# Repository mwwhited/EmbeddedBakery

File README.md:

# Embedded Bakery

## Summary

This is a collection of various electronics and microprocessor projects including PAL, FPGA, CPLD, and microcontroller experiments.

## Repository Structure

```
src/
├── arduino/          # Arduino sketches and libraries
├── AVR/              # AVR microcontroller projects (ATmega, ATtiny)
├── ESP8266/          # ESP8266 WiFi module projects
├── STM32/            # STM32 ARM microcontroller projects
├── PIC/              # Microchip PIC microcontroller projects
├── xilinx/           # Xilinx FPGA projects (Arty A7, Arty Z7)
├── altera/           # Altera/Intel FPGA projects (Cyclone II)
├── GenericFPGA/      # Reusable FPGA IP cores
├── pal/              # Programmable Array Logic projects
├── basicstamp/       # Basic Stamp projects
├── particle/         # Particle IoT projects
└── tools/            # Development tools (.NET solution)
circuits/             # KiCad PCB designs and schematics
notes/                # Reference documentation and datasheets
```

## Key Projects

### Microcontroller Projects
- **Arduino**: Various sensor interfaces, relay controllers, FreeRTOS examples, LANC camera control
- **ESP8266**: LXI Serial Bridge, WiFi relay controllers, network interfaces
- **AVR**: Bare-metal ATmega/ATtiny projects, digital clock
- **STM32**: Blue Pill development projects
- **PIC**: PIC16F627 LED chase patterns

### FPGA Projects
- **Xilinx Arty A7**: MicroBlaze tutorials, custom CPU designs, Pmod interfaces
- **Xilinx Arty Z7**: Zynq HLS tutorials
- **Altera Cyclone II**: Basic FPGA experiments
- **XC9500 CPLD**: Legacy CPLD projects

### PCB Designs
- Analog computer circuits
- Development boards
- Interface adapters (LANC, RS485, H4n)

### Development Tools
- BinaryBaker: ROM/PROM utilities
- MicroCodeBuilder: Custom CPU microcode tools
- TruthExpander: Boolean logic tools

## Getting Started

See individual project README files for specific build instructions.

### Quick Reference

| Platform | Build Tool |
|----------|------------|
| Arduino | Arduino IDE / arduino-cli |
| AVR | WinAVR / avr-gcc + avrdude |
| ESP8266 | PlatformIO / Arduino IDE |
| STM32 | STM32duino / STM32CubeIDE |
| PIC | MPLAB X + XC8 |
| Xilinx | Vivado / ISE |
| Altera | Quartus |
| KiCad | KiCad + KiBot |
| .NET | dotnet CLI / Visual Studio |

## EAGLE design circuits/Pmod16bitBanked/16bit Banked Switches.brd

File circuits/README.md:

# Circuit and PCB Projects

KiCad PCB designs and schematics.

## Projects

### Altair8800
Altair 8800 computer clone PCB.

### AnalogCalculator
Analog computer/calculator circuits including:
- Op-amp based computing boards
- Comdyna GP-6 clone
- Diode function generators
- Fast ADC

### Atmega32DevKit
ATmega32 development kit PCB.

### ComdynaGP6
Comdyna GP-6 analog computer clone components.

### Digital Tools
Digital logic development boards.

### DiodeLogicBoards
Discrete diode logic circuits:
- 1-byte register
- Address decoder (4 to 16)
- Input/output boards
- PROM emulator

### Favero
Favero fencing scoring machine interface.

### HelperBoards
Utility boards:
- 10x10 switch matrix
- Potentiometer boards
- Analog controller boards
- Waveform generator amplifier

### ITT_Phone
Rotary phone interface board.

### MyIOShield
Custom I/O shield PCB.

### Navtec
NavTec interface board.

### Pmod16bitBanked
16-bit banked switch Pmod board.

### PmodLED8x8
8x8 LED matrix Pmod board.

### RC-004 Clone
RC-004 clone circuit.

### SG_Power
Power supply board.

### SimpleClock
Simple clock circuit.

### greaseweazle
Greaseweazle floppy disk interface case/board.

### h4n2rs485
Zoom H4n to RS485 interface.

### i8051
8051 microcontroller development kit.

### lanc2rs485
LANC to RS485 converter.

## KiCad Libraries

### MyCustomSymbols.kicad_sym
Custom schematic symbols.

### MyCustomLibrary.pretty/
Custom PCB footprints.

### KicadSymbols/
Additional symbol libraries.

## Build Documentation

Use KiBot to generate documentation:
```bash
kibot -c ../docs.kibot.yaml
```

## Tools

- **KiCad** - Schematic capture and PCB layout
- **KiBot** - Automated documentation generation

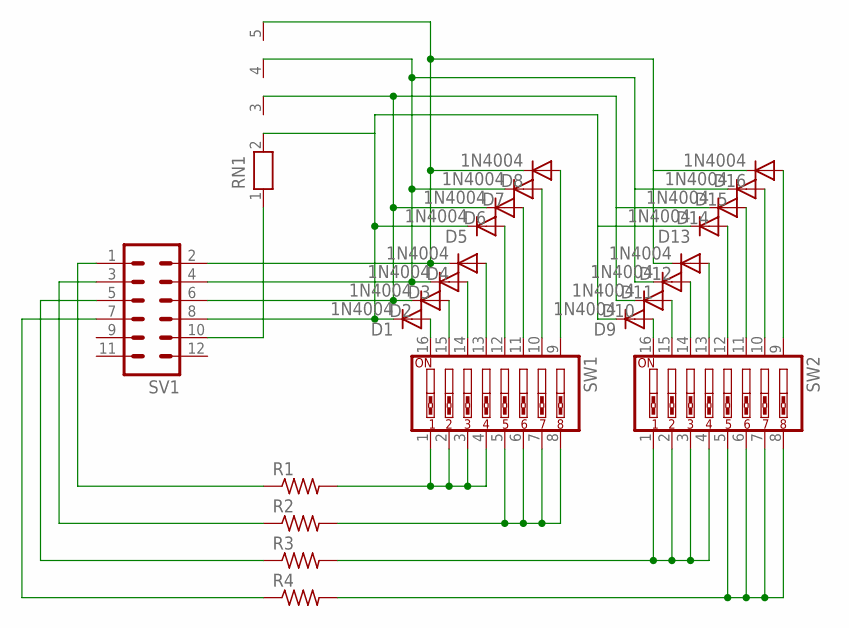
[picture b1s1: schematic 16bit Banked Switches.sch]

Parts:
D1, D2, D3, D4, D5, D6, D7, D8, D9, D10, D11, D12, D13, D14, D15, D16: 1N4004; DO41-10
R1, R2, R3, R4: R-US_0207/9; 0207/9
RN1: RN04; RN-5
SV1: MA06-2
SW1, SW2: SW_DIP-8; EDG-08

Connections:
unnamed: R1.2, SW1.1, SW1.2, SW1.3, SW1.4
unnamed: R2.2, SW1.5, SW1.6, SW1.7, SW1.8
unnamed: R3.2, SW2.1, SW2.2, SW2.3, SW2.4
unnamed: R4.2, SW2.5, SW2.6, SW2.7, SW2.8
unnamed: D4.C, D8.C, D12.C, D16.C, RN1.5, SV1.2
unnamed: D1.A, SW1.16
unnamed: D2.A, SW1.15
unnamed: D3.A, SW1.14
unnamed: D4.A, SW1.13
unnamed: D5.A, SW1.12
unnamed: D6.A, SW1.11
unnamed: D7.A, SW1.10
unnamed: D8.A, SW1.9
unnamed: D9.A, SW2.16
unnamed: D10.A, SW2.15
unnamed: D11.A, SW2.14
unnamed: D12.A, SW2.13
unnamed: D13.A, SW2.12
unnamed: D14.A, SW2.11
unnamed: D15.A, SW2.10
unnamed: D16.A, SW2.9
unnamed: D1.C, D5.C, D9.C, D13.C, RN1.2, SV1.8
unnamed: D2.C, D6.C, D10.C, D14.C, RN1.3, SV1.6
unnamed: D3.C, D7.C, D11.C, D15.C, RN1.4, SV1.4
unnamed: R1.1, SV1.1
unnamed: RN1.1, SV1.10
unnamed: R2.1, SV1.3
unnamed: R3.1, SV1.5
unnamed: R4.1, SV1.7

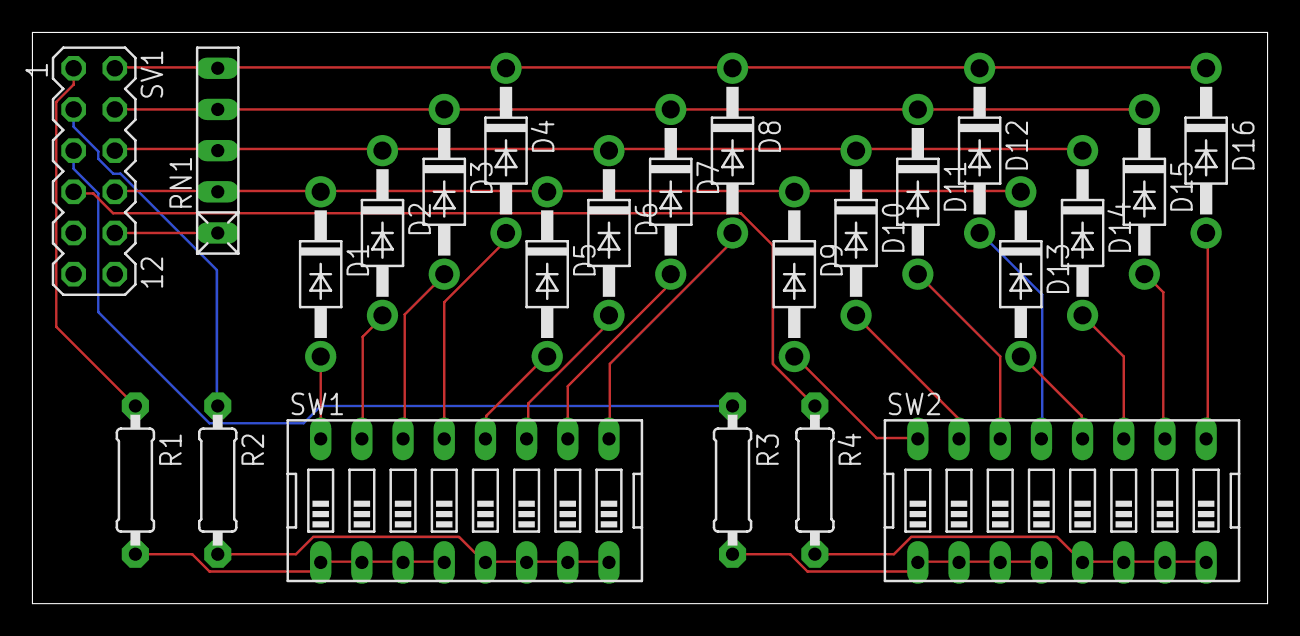
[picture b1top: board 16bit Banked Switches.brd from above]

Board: 2 copper layers, 76.2 x 35.2 mm, 24 parts (0 on the bottom side), 29 nets.

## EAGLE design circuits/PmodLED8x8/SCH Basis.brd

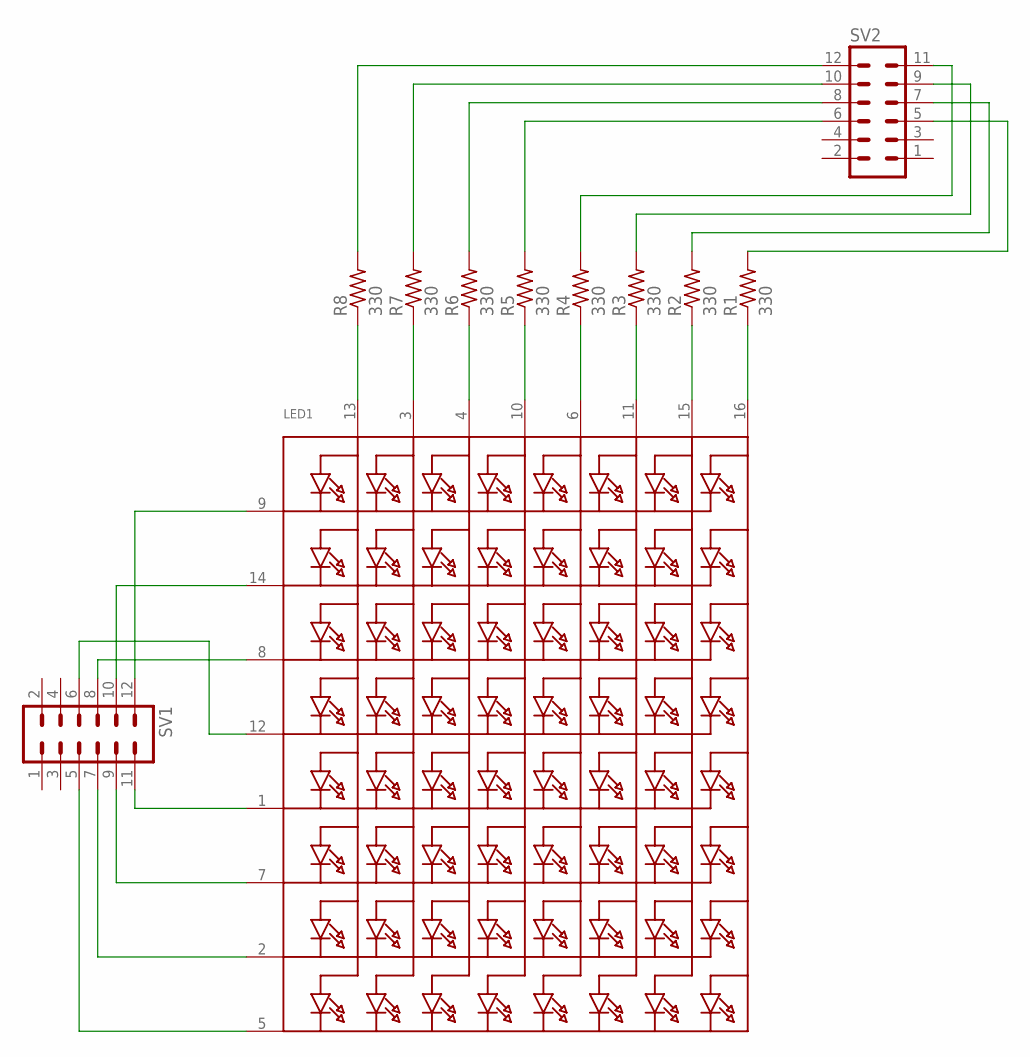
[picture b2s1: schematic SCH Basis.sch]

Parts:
LED1: SEGMENT_8X8_ROWCATHODEM12A881UR; SEGMENT_BL-M12A881UR
R1, R2, R3, R4, R5, R6, R7, R8: 330; 0207/9
SV1, SV2: MA06-2

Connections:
unnamed: LED1.13 (A1), R8.1
unnamed: LED1.3 (A2), R7.1
unnamed: LED1.4 (A3), R6.1
unnamed: LED1.10 (A4), R5.1
unnamed: LED1.6 (A5), R4.1
unnamed: LED1.11 (A6), R3.1
unnamed: LED1.15 (A7), R2.1
unnamed: LED1.16 (A8), R1.1
unnamed: R8.2, SV2.12
unnamed: R7.2, SV2.10
unnamed: R6.2, SV2.8
unnamed: R5.2, SV2.6
unnamed: R4.2, SV2.11
unnamed: R3.2, SV2.9
unnamed: R2.2, SV2.7
unnamed: R1.2, SV2.5
unnamed: LED1.9 (K1), SV1.12
unnamed: LED1.14 (K2), SV1.10
unnamed: LED1.8 (K3), SV1.8
unnamed: LED1.12 (K4), SV1.6
unnamed: LED1.1 (K5), SV1.11
unnamed: LED1.7 (K6), SV1.9
unnamed: LED1.2 (K7), SV1.7
unnamed: LED1.5 (K8), SV1.5

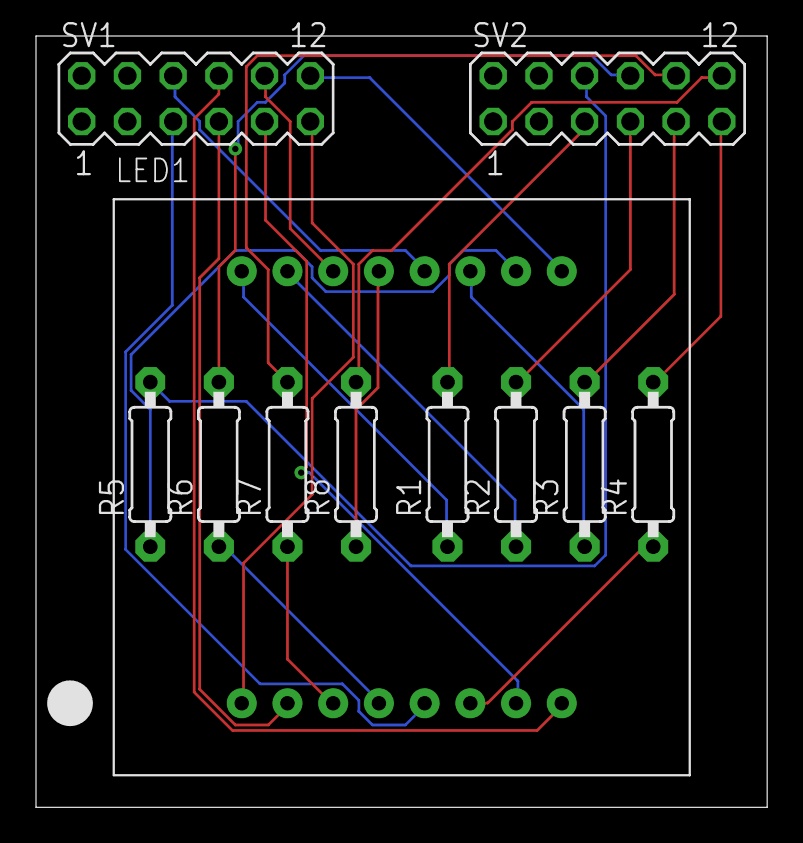
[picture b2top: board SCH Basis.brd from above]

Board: 2 copper layers, 40.6 x 42.9 mm, 11 parts (0 on the bottom side), 24 nets.

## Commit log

2020-11-25 first push
2020-11-26 Found more good stuff
2020-12-02 update diagrams and import some other code
2020-12-02 Update kicad layouts
2020-12-16 Update diagrams for fencing machine interfaces
2021-01-15 arty test code
2021-01-16 clean up
2021-01-30 udpate model
2021-01-31 Create ARTY A7 Test Project
2021-02-01 update designs
2021-02-18 Add arty test projects
2021-02-18 Update arty 100 default constraints file
2021-02-18 converted demo for pmodenc to support Arty
2021-02-19 start a rom editor
2021-02-21 working on similar calculator
2021-02-21 clock divider is now working
2021-02-21 Got keypad working
2021-02-22 keypad working, started registers
2021-02-22 create nibble reader
2021-02-22 create nibble writer
2021-02-24 Create a test i2c module
2021-02-24 i2c write single byte
2021-02-24 changed i2c to use High-Z instead of being driven high.
2021-02-25 Start statemachine for i2c lcd
2021-02-25 test creating a custom IP for the IP Catalog
2021-02-25 Revert "test creating a custom IP for the IP Catalog"
    This reverts commit c07ab34091df91f1932734a7cfe39c503ffb506f.
2021-02-25 Add old arduino test projects
2021-02-25 Add old Xilinx xc9500 CPLD projects
2021-02-25 update quartus/ep2c5 projects
2021-02-25 Started RowColumnDecoder as shared IP
2021-03-01 Fixed Row Column Decoder to make synthesis possible
2021-03-01 update vivado package for rowcolumndecoder
2021-03-02 repackage row col decoder
2021-03-03 Create simple clock divider IP
2021-03-03 clean up simulation
2021-03-03 Fix row decoder
2021-03-03 update Ip Catalog for RowColumnDecoder
2021-03-03 update row column decoder
2021-03-03 change simple calc to use shared ip catalog
2021-03-04 cleanup and start my own VGA
2021-03-04 My VGA code works for a test pattern
2021-03-04 not quite right... but time for sleep
2021-03-04 vga test run ... its alive!
2021-03-04 cleaned up text mode.. made it a mod4 versus mod3... looks much cleaner.
2021-03-05 vga update
2021-03-05 Create IP for PMOD VGA Text Mode
2021-03-05 Create IP for PMOD VGA Text Mode 2
2021-03-05 create custom pmodkypd based on rowcolumndecoder
2021-03-05 try VGA as IP
2021-03-10 rollback VGA from Calc and IP
2021-03-10 axi mig ddr tutorial
2021-03-11 clean up ip and start emulator
2021-03-11 another try ad character rom
2021-03-12 create character rom unit
2021-03-12 color matrix
2021-03-12 color matrix combinational
2021-03-12 color palette combinational
2021-03-13 text rendering
2021-03-13 text mode
2021-03-13 add change detection to row column decoder
2021-03-13 add change detection to row column IP package
2021-03-13 update and cleanup child IP for PMod Keypad
2021-03-13 update and cleanup child IP for PMod Keypad again
2021-03-14 Add change detection to rew/column decoder
2021-03-14 update ip package to include change detection to rew/column decoder
2021-03-14 added change detection to pmod keypad ip
2021-03-14 start working on fifo
2021-03-14 progress
2021-03-15 still working on fifo/keyboard buffer
2021-03-16 update keypad
2021-03-16 make keypad work again
2021-03-17 fifo test
2021-03-18 fifo example
2021-03-18 fifo example... progress, at least reset works
2021-03-18 FIFO Example is working!
2021-03-18 Extend constaints file to support pmod shield
2021-03-20 IT WORKS! ... Keypad FIFO writing works!
2021-03-20 Triggered FIFO Writed IP Created
2021-03-21 FIFO to BRAM works
2021-03-22 Remove old files
2021-03-22 clean up IP
2021-03-22 Clean up Arty constraints
2021-03-22 working on text rendering with fifo/blockram
2021-03-29 fix up
2021-03-31 test custom pmod led 8x8
2021-03-31 test custom pmod 16bit switch banked
2021-03-31 copy in schematics for custom pmods
2021-03-31 remove remapping and add rotation
2021-04-03 fix up 16 bit banked key
2021-04-11 update pmod16bit
2022-12-09 update changes. at pic playground
2022-12-13 add other projects
2022-12-13 change back to 10 bit and fix variables
2023-01-01 update examples for ESP-01, ESP32, Particle Spark Core/Photon
2023-01-01 update notes
2023-01-02 stub out clock for attiny2313
2023-01-02 Bump System.Drawing.Common in /src/tools/BinaryBaker/RomFonts
    Bumps [System.Drawing.Common](https://github.com/dotnet/runtime) from 5.0.1 to 5.0.3.
    - [Release notes](https://github.com/dotnet/runtime/releases)
    - [Commits](https://github.com/dotnet/runtime/compare/v5.0.1...v5.0.3)
    ---
    updated-dependencies:
    - dependency-name: System.Drawing.Common
2023-01-02 Bump System.Drawing.Common in /src/tools/BinaryBaker/ImageBuilder
    Bumps [System.Drawing.Common](https://github.com/dotnet/runtime) from 5.0.1 to 5.0.3.
    - [Release notes](https://github.com/dotnet/runtime/releases)
    - [Commits](https://github.com/dotnet/runtime/compare/v5.0.1...v5.0.3)
    ---
    updated-dependencies:
    - dependency-name: System.Drawing.Common
2023-01-02 using internal oscillator and default multiplier
2023-01-02 update time
2023-01-03 clock working
2023-01-03 sketch up circuits
2023-01-07 update clock
2023-01-07 Fix schematics and coding
2023-01-07 update design
2023-01-07 update readme for simple clock
2023-02-21 add stuff
2023-02-22 Add scripts and update controller code
2023-03-08 build out circuits
2023-03-08 add circuits
2023-03-08 update circuits
2023-03-08 cleanup circuits
2023-03-08 Add helper boards
2023-03-09 update layount
2023-03-09 update analog computer layout
2023-03-19 migrate old code
2023-03-19 swap out SD.h for SDFat.h
2023-03-27 update and save PDF files
2023-03-30 update libraries, stub out example IO board pcb, start looking at freertos
2023-04-23 update libraries
2023-04-23 stub out stm32 example
2023-04-23 try arduino blen micro redbearlab
2023-04-23 add mapping
2023-04-24 Add ring buffer library and stub out RTOS example
2023-04-24 update script
2023-04-26 update keyboard
2023-04-27 update examples
2023-05-01 update keyboard mapping
2023-10-11 add examples
2025-01-15 first pass
2025-01-18 more toys
2025-01-18 pile of hacks
2025-01-24 update microcode builder
2025-01-24 Improve MicroCode def
2025-01-31 update table
2025-01-31 update micro code
2025-02-08 update frameworks
2025-02-14 Update LICENSE
2025-02-16 update references
2025-03-24 add analog converter
2025-05-01 add timer
2025-05-01 add the ability to disable logging
2025-05-02 change to support multiple devices
2025-05-02 update code
2025-05-02 update timer
2025-05-03 add debugging
2025-05-03 fix logging and support multiple boards with the same pinout
2025-05-03 update changes adding watchdog timer, input validation and time remaining
2025-05-03 this dont wont
2025-05-03 change pinout
2025-05-03 add show all settings
2025-08-01 Auto-commit:
2025-08-04 update arduino libs
2025-12-06 working
2025-12-06 migrate
2025-12-13 start notes
2025-12-13 review and describe projects
2025-12-26 update phase1 AI
2025-12-26 start line follower hack
2026-01-08 update all
2026-01-09 add 8051
2026-01-09 add .net micro framework projects
2026-01-09 migrated
2026-04-09 Add more designs
